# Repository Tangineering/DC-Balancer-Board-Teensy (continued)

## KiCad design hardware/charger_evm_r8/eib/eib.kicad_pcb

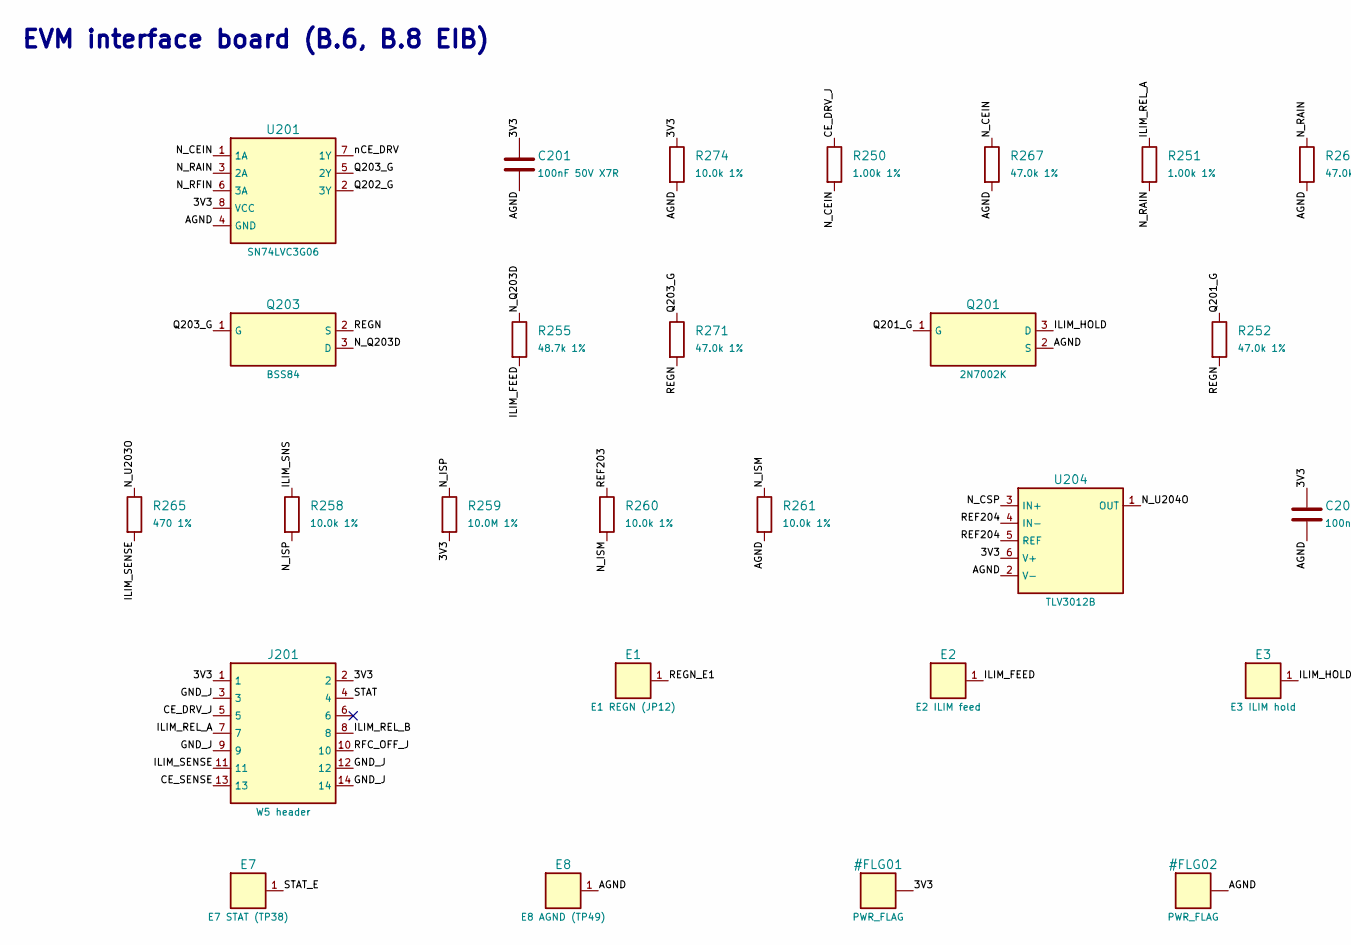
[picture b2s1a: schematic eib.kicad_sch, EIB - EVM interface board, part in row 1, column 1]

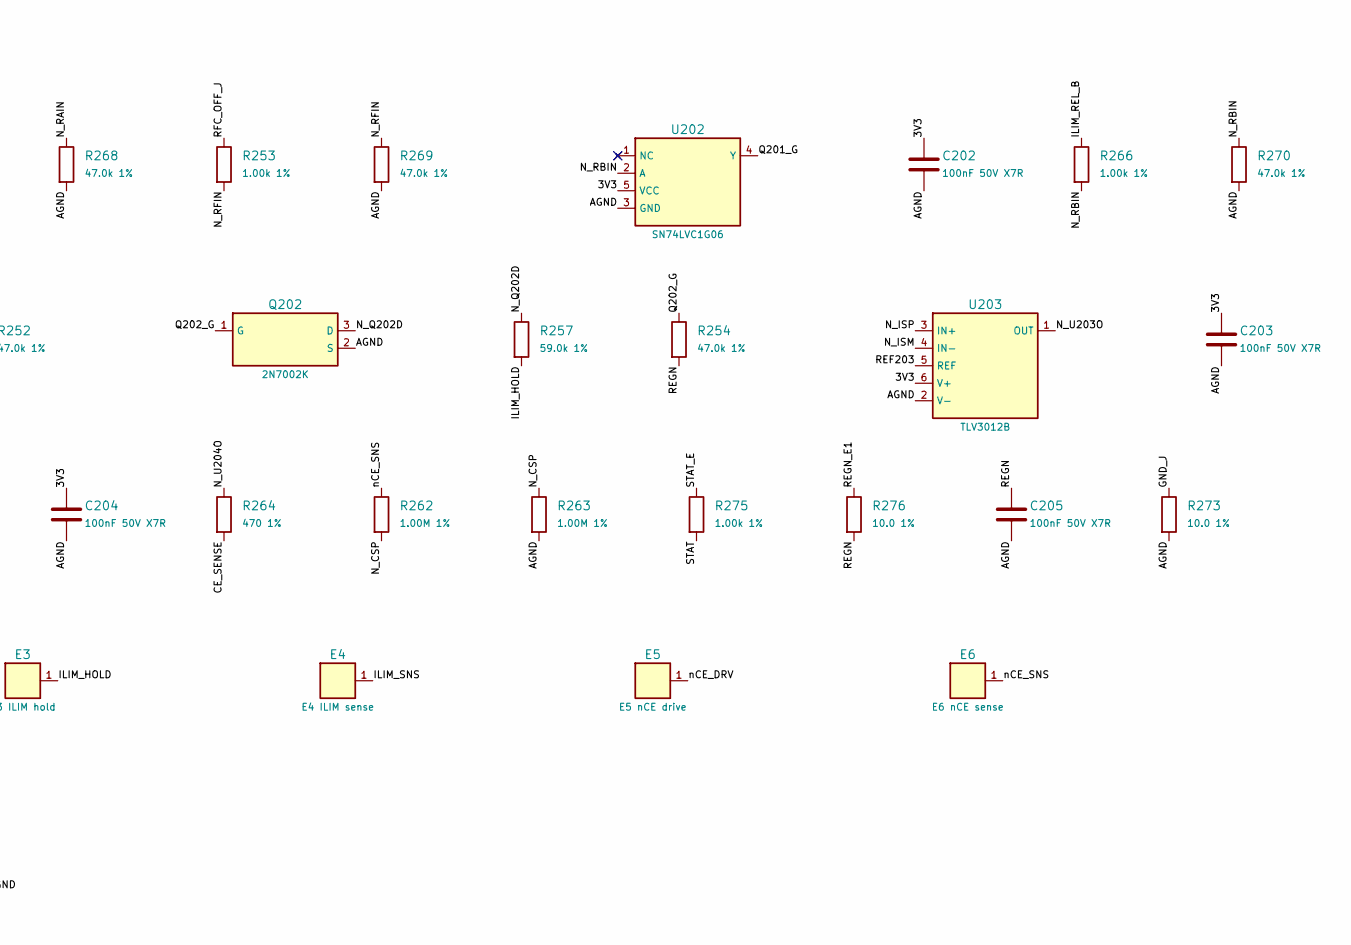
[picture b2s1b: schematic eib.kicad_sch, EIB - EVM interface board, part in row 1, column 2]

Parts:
C201, C202, C203, C204, C205: 100nF 50V X7R; C_0603_1608Metric_CrtYd0.10; MPN GRM188R71H104KA93D
E1: E1 REGN (JP12); LeadPad_PTH_D1.0mm_P1.8mm
E2: E2 ILIM feed; LeadPad_PTH_D1.0mm_P1.8mm
E3: E3 ILIM hold; LeadPad_PTH_D1.0mm_P1.8mm
E4: E4 ILIM sense; LeadPad_PTH_D1.0mm_P1.8mm
E5: E5 nCE drive; LeadPad_PTH_D1.0mm_P1.8mm
E6: E6 nCE sense; LeadPad_PTH_D1.0mm_P1.8mm
E7: E7 STAT (TP38); LeadPad_PTH_D1.0mm_P1.8mm
E8: E8 AGND (TP49); LeadPad_PTH_D1.0mm_P1.8mm
J201: W5 header; Samtec_FTSH-107-01-DV_2x07_P1.27mm_SMD; MPN Samtec FTSH/SHF-107 class (T-A-05)
Q201, Q202: 2N7002K; SOT-23_CrtYd0.10; MPN 2N7002KT1G
Q203: BSS84; SOT-23_CrtYd0.10; MPN BSS84LT1G
R250, R251, R253, R266, R275: 1.00k 1%; R_0603_1608Metric_CrtYd0.10; MPN CRCW06031K00FKEA
R252, R254, R267, R268, R269, R270, R271: 47.0k 1%; R_0603_1608Metric_CrtYd0.10; MPN CRCW060347K0FKEA
R255: 48.7k 1%; R_0603_1608Metric_CrtYd0.10; MPN CRCW060348K7FKEA
R257: 59.0k 1%; R_0603_1608Metric_CrtYd0.10; MPN CRCW060359K0FKEA
R258, R260, R261, R274: 10.0k 1%; R_0603_1608Metric_CrtYd0.10; MPN CRCW060310K0FKEA
R259: 10.0M 1%; R_0603_1608Metric_CrtYd0.10; MPN CRCW060310M0FKEA
R262, R263: 1.00M 1%; R_0603_1608Metric_CrtYd0.10; MPN CRCW06031M00FKEA
R264, R265: 470 1%; R_0603_1608Metric_CrtYd0.10; MPN CRCW0603470RFKEA
R273, R276: 10.0 1%; R_0603_1608Metric_CrtYd0.10; MPN CRCW060310R0FKEA
U201: SN74LVC3G06; Texas_DCT0008A_SSOP-8_TI-land_CrtYd0.10; MPN SN74LVC3G06DCTR
U202: SN74LVC1G06; Texas_DCK-5_SC-70-5_CrtYd0.10; MPN SN74LVC1G06DCKR
U203, U204: TLV3012B; SOT-23-6_CrtYd0.10; MPN TLV3012BIDBVR

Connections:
/3V3: C201.1, C202.1, C203.1, C204.1, J201.1, J201.2, R259.2, R274.1, U201.8 (VCC), U202.5 (VCC), U203.6 (V+), U204.6 (V+)
/AGND: C201.2, C202.2, C203.2, C204.2, C205.2, E8.1, Q201.2 (S), Q202.2 (S), R261.2, R263.2, R267.2, R268.2, R269.2, R270.2, R273.2, R274.2, U201.4 (GND), U202.3 (GND), U203.2 (V-), U204.2 (V-)
/CE_DRV_J: J201.5, R250.1
/CE_SENSE: J201.13, R264.2
/GND_J: J201.3, J201.9, J201.12, J201.14, R273.1
/ILIM_FEED: E2.1, R255.2
/ILIM_HOLD: E3.1, Q201.3 (D), R257.2
/ILIM_REL_A: J201.7, R251.1
/ILIM_REL_B: J201.8, R266.1
/ILIM_SENSE: J201.11, R265.2
/ILIM_SNS: E4.1, R258.1
/N_CEIN: R250.2, R267.1, U201.1 (1A)
/N_CSP: R262.2, R263.1, U204.3 (IN+)
/N_ISM: R260.2, R261.1, U203.4 (IN-)
/N_ISP: R258.2, R259.1, U203.3 (IN+)
/N_Q202D: Q202.3 (D), R257.1
/N_Q203D: Q203.3 (D), R255.1
/N_RAIN: R251.2, R268.1, U201.3 (2A)
/N_RBIN: R266.2, R270.1, U202.2 (A)
/N_RFIN: R253.2, R269.1, U201.6 (3A)
/N_U203O: R265.1, U203.1 (OUT)
/N_U204O: R264.1, U204.1 (OUT)
/Q201_G: Q201.1 (G), R252.1, U202.4 (Y)
/Q202_G: Q202.1 (G), R254.1, U201.2 (3Y)
/Q203_G: Q203.1 (G), R271.1, U201.5 (2Y)
/REF203: R260.1, U203.5 (REF)
/REF204: U204.4 (IN-), U204.5 (REF)
/REGN: C205.1, Q203.2 (S), R252.2, R254.2, R271.2, R276.2
/REGN_E1: E1.1, R276.1
/RFC_OFF_J: J201.10, R253.1
/STAT: J201.4, R275.2
/STAT_E: E7.1, R275.1
/nCE_DRV: E5.1, U201.7 (1Y)
/nCE_SNS: E6.1, R262.1

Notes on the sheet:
EVM interface board (B.6, B.8 EIB)

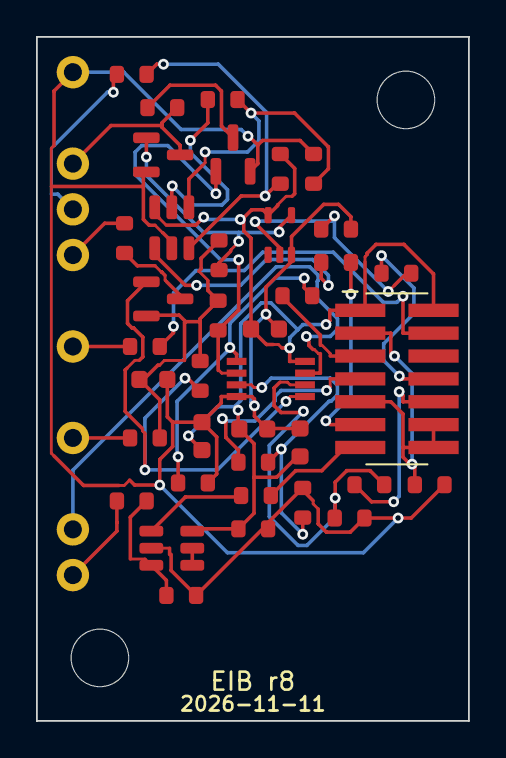
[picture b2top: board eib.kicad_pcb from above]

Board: 2 copper layers, 24.0 x 38.0 mm, 48 parts (0 on the bottom side), 34 nets.

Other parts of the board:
H1, H2: MountingHole_3.2mm_M3_KeepOut7mm
